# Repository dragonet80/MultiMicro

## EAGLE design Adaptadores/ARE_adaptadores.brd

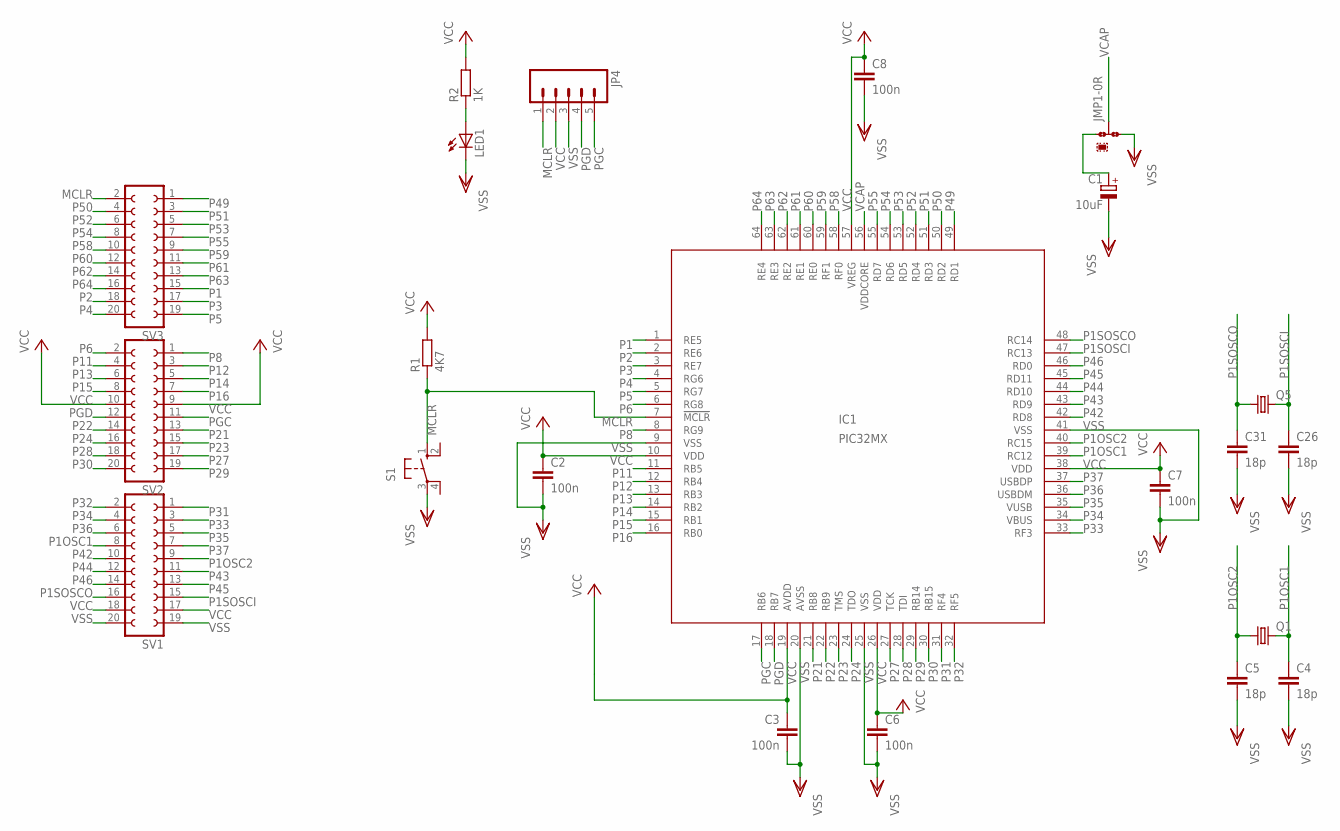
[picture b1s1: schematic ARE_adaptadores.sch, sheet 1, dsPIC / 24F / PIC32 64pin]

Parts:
C1: 10uF; SMC_C
C2, C3, C6, C7, C8: 100n; C0805
C4, C5, C26, C31: 18p; C0805
IC1: PIC32MX; TQFP64-10X10
JMP1: 0R-JUMPA; A0R-JMP
JP4: M05PTH; 1X05
LED1: LEDCHIPLED_0805; CHIPLED_0805
Q1, Q5: CRYSTALHC18U-V; HC18U-V
R1: 4K7; R0805
R2: 1K; R0805
S1: 10-XX; B3F-10XX; MPN B3F-1000
SV1, SV2, SV3: FE10-2W

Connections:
MCLR: IC1.7 (!MCLR), JP4.1, R1.1, S1.1 (S), SV3.2
unnamed: LED1.A, R2.1
unnamed: C1.+, JMP1.1
P1: IC1.1 (RE5), SV3.15
P1OSC1: C4.1, IC1.39 (RC12), Q1.2, SV1.8
P1OSC2: C5.1, IC1.40 (RC15), Q1.1, SV1.9
P1SOSCI: C26.1, IC1.47 (RC13), Q5.2, SV1.15
P1SOSCO: C31.1, IC1.48 (RC14), Q5.1, SV1.16
P2: IC1.2 (RE6), SV3.18
P3: IC1.3 (RE7), SV3.17
P4: IC1.4 (RG6), SV3.20
P5: IC1.5 (RG7), SV3.19
P6: IC1.6 (RG8), SV2.2
P8: IC1.8 (RG9), SV2.1
P11: IC1.11 (RB5), SV2.4
P12: IC1.12 (RB4), SV2.3
P13: IC1.13 (RB3), SV2.6
P14: IC1.14 (RB2), SV2.5
P15: IC1.15 (RB1), SV2.8
P16: IC1.16 (RB0), SV2.7
P21: IC1.21 (RB8), SV2.13
P22: IC1.22 (RB9), SV2.14
P23: IC1.23 (TMS), SV2.15
P24: IC1.24 (TDO), SV2.16
P27: IC1.27 (TCK), SV2.17
P28: IC1.28 (TDI), SV2.18
P29: IC1.29 (RB14), SV2.19
P30: IC1.30 (RB15), SV2.20
P31: IC1.31 (RF4), SV1.1
P32: IC1.32 (RF5), SV1.2
P33: IC1.33 (RF3), SV1.3
P34: IC1.34 (VBUS), SV1.4
P35: IC1.35 (VUSB), SV1.5
P36: IC1.36 (USBDM), SV1.6
P37: IC1.37 (USBDP), SV1.7
P42: IC1.42 (RD8), SV1.10
P43: IC1.43 (RD9), SV1.11
P44: IC1.44 (RD10), SV1.12
P45: IC1.45 (RD11), SV1.13
P46: IC1.46 (RD0), SV1.14
P49: IC1.49 (RD1), SV3.1
P50: IC1.50 (RD2), SV3.4
P51: IC1.51 (RD3), SV3.3
P52: IC1.52 (RD4), SV3.6
P53: IC1.53 (RD5), SV3.5
P54: IC1.54 (RD6), SV3.8
P55: IC1.55 (RD7), SV3.7
P58: IC1.58 (RF0), SV3.10
P59: IC1.59 (RF1), SV3.9
P60: IC1.60 (RE0), SV3.12
P61: IC1.61 (RE1), SV3.11
P62: IC1.62 (RE2), SV3.14
P63: IC1.63 (RE3), SV3.13
P64: IC1.64 (RE4), SV3.16
PGC: IC1.17 (RB6), JP4.5, SV2.11
PGD: IC1.18 (RB7), JP4.4, SV2.12
VCAP: IC1.56 (VDDCORE), JMP1.2
VCC: C2.1, C3.1, C6.1, C7.1, C8.1, IC1.10 (VDD), IC1.19 (AVDD), IC1.26 (VDD), IC1.38 (VDD), IC1.57 (VREG), JP4.2, R1.2, R2.2, SV1.17, SV1.18, SV2.9, SV2.10; also elsewhere on the board
VSS: C1.-, C2.2, C3.2, C4.2, C5.2, C6.2, C7.2, C8.2, C26.2, C31.2, IC1.9 (VSS), IC1.20 (AVSS), IC1.25 (VSS), IC1.41 (VSS), JMP1.3, JP4.3, LED1.C, S1.3, SV1.19, SV1.20; also elsewhere on the board

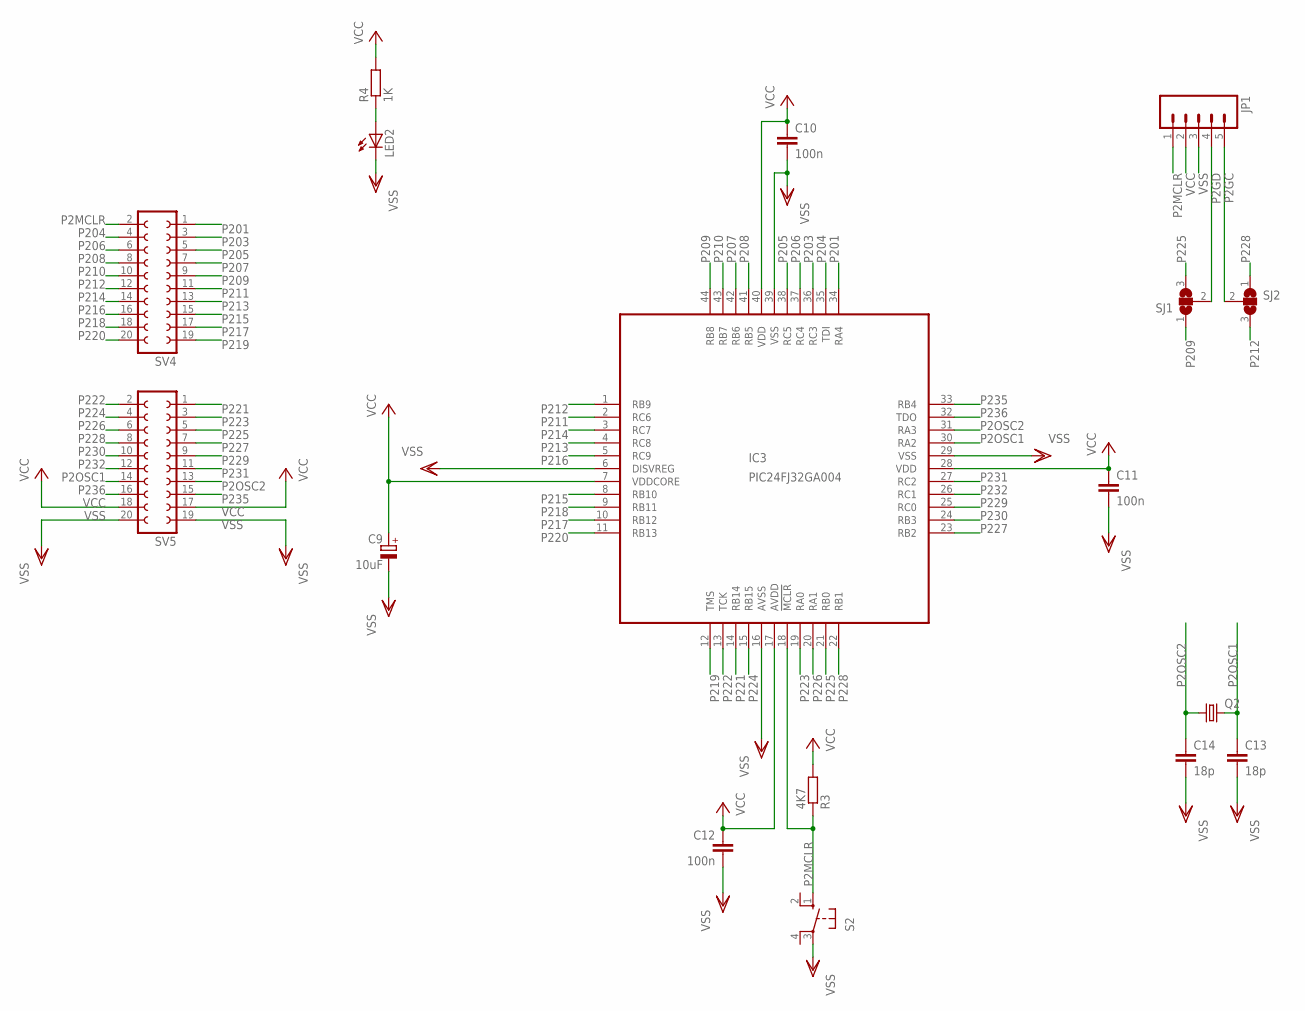
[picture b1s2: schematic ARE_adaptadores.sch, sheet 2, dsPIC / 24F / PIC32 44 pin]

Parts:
C9: 10uF; SMC_C
C10, C11, C12: 100n; C0805
C13, C14: 18p; C0805
IC3: PIC24FJ32GA004; TQFP44
JP1: M05PTH; 1X05
LED2: LEDCHIPLED_0805; CHIPLED_0805
Q2: CRYSTALHC18U-V; HC18U-V
R3: 4K7; R0805
R4: 1K; R0805
S2: 10-XX; B3F-10XX; MPN B3F-1000
SJ1, SJ2: SJ2W; SJ_2
SV4, SV5: FE10-2W

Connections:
unnamed: LED2.A, R4.1
P2GC: JP1.5, SJ2.2
P2GD: JP1.4, SJ1.2
P2MCLR: IC3.18 (!MCLR), JP1.1, R3.1, S2.1 (S), SV4.2
P2OSC1: C13.1, IC3.30 (RA2), Q2.2, SV5.14
P2OSC2: C14.1, IC3.31 (RA3), Q2.1, SV5.13
P201: IC3.34 (RA4), SV4.1
P203: IC3.36 (RC3), SV4.3
P204: IC3.35 (TDI), SV4.4
P205: IC3.38 (RC5), SV4.5
P206: IC3.37 (RC4), SV4.6
P207: IC3.42 (RB6), SV4.7
P208: IC3.41 (RB5), SV4.8
P209: IC3.44 (RB8), SJ1.1, SV4.9
P210: IC3.43 (RB7), SV4.10
P211: IC3.2 (RC6), SV4.11
P212: IC3.1 (RB9), SJ2.3, SV4.12
P213: IC3.4 (RC8), SV4.13
P214: IC3.3 (RC7), SV4.14
P215: IC3.8 (RB10), SV4.15
P216: IC3.5 (RC9), SV4.16
P217: IC3.10 (RB12), SV4.17
P218: IC3.9 (RB11), SV4.18
P219: IC3.12 (TMS), SV4.19
P220: IC3.11 (RB13), SV4.20
P221: IC3.14 (RB14), SV5.1
P222: IC3.13 (TCK), SV5.2
P223: IC3.19 (RA0), SV5.3
P224: IC3.15 (RB15), SV5.4
P225: IC3.21 (RB0), SJ1.3, SV5.5
P226: IC3.20 (RA1), SV5.6
P227: IC3.23 (RB2), SV5.7
P228: IC3.22 (RB1), SJ2.1, SV5.8
P229: IC3.25 (RC0), SV5.9
P230: IC3.24 (RB3), SV5.10
P231: IC3.27 (RC2), SV5.11
P232: IC3.26 (RC1), SV5.12
P235: IC3.33 (RB4), SV5.15
P236: IC3.32 (TDO), SV5.16
VCC: C9.+, C10.1, C11.1, C12.1, IC3.7 (VDDCORE), IC3.17 (AVDD), IC3.28 (VDD), IC3.40 (VDD), JP1.2, R3.2, R4.2, SV5.17, SV5.18; also elsewhere on the board
VSS: C9.-, C10.2, C11.2, C12.2, C13.2, C14.2, IC3.6 (DISVREG), IC3.16 (AVSS), IC3.29 (VSS), IC3.39 (VSS), JP1.3, LED2.C, S2.3, SV5.19, SV5.20; also elsewhere on the board

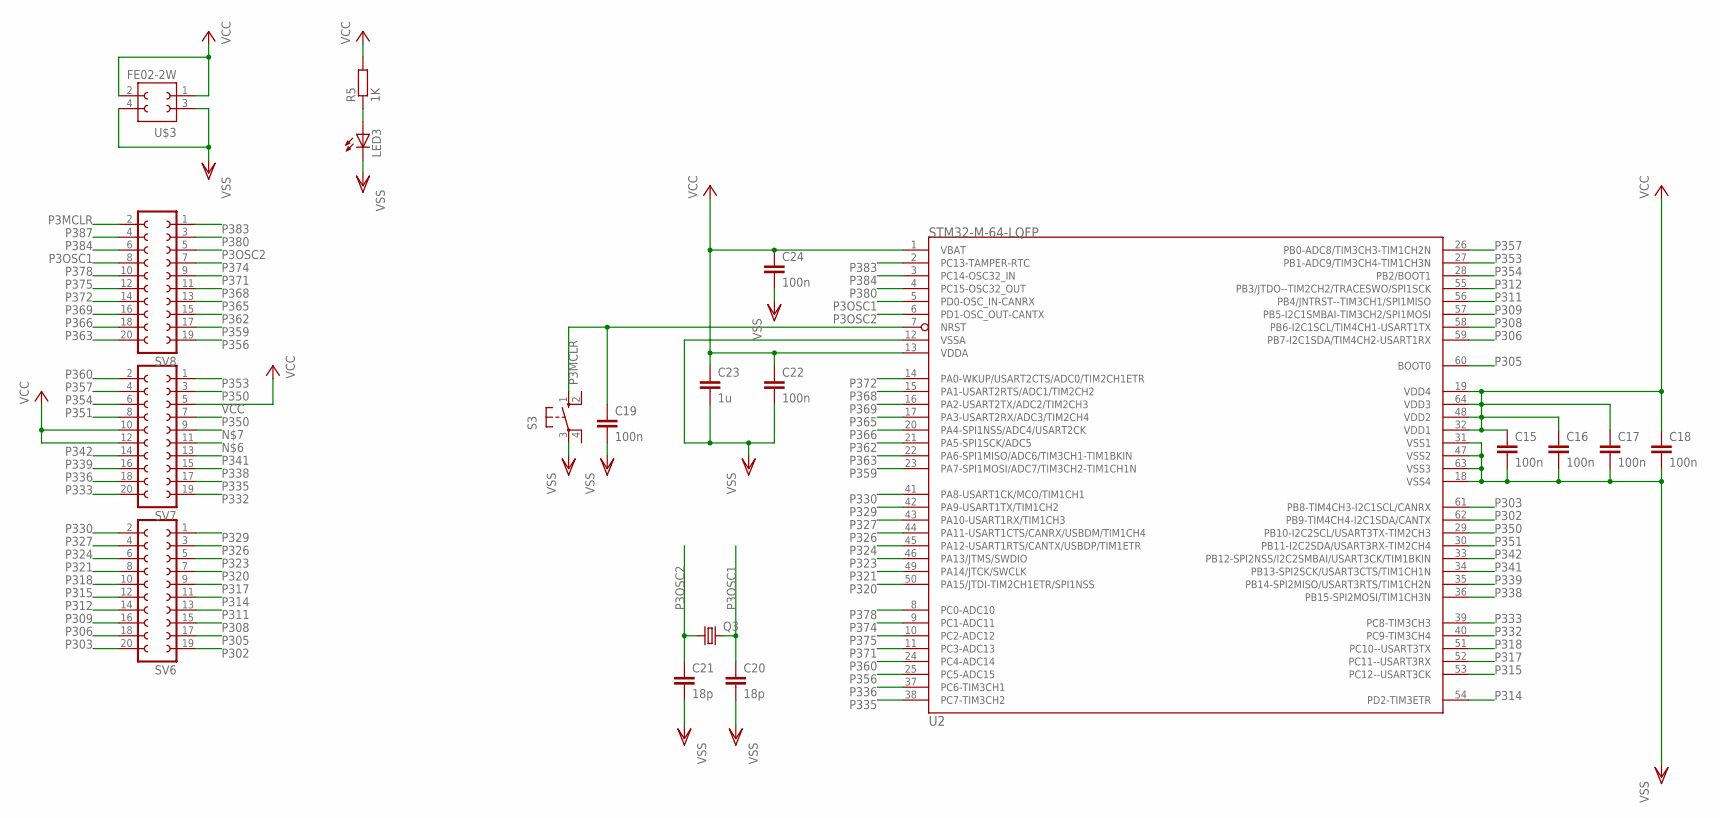
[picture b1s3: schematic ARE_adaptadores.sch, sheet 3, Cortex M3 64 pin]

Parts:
C15, C16, C17, C18, C19, C22, C24: 100n; C0805
C20, C21: 18p; C0805
C23: 1u; C0805
LED3: LEDCHIPLED_0805; CHIPLED_0805
Q3: CRYSTALHC18U-V; HC18U-V
R5: 1K; R0805
S3: 10-XX; B3F-10XX; MPN B3F-1000
SV6, SV7, SV8: FE10-2W
U2: STM32-M-64-LQFP; LQFP64
U$3: FE02-2W

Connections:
unnamed: LED3.A, R5.1
P3MCLR: C19.1, S3.1 (S), SV8.2, U2.7 (NRST)
P3OSC1: C20.1, Q3.2, SV8.8, U2.5 (PD0-OSC_IN-CANRX)
P3OSC2: C21.1, Q3.1, SV8.5, U2.6 (PD1-OSC_OUT-CANTX)
P302: SV6.19, U2.62 (PB9-TIM4CH4-I2C1SDA/CANTX)
P303: SV6.20, U2.61 (PB8-TIM4CH3-I2C1SCL/CANRX)
P305: SV6.17, U2.60 (BOOT0)
P306: SV6.18, U2.59 (PB7-I2C1SDA/TIM4CH2-USART1RX)
P308: SV6.15, U2.58 (PB6-I2C1SCL/TIM4CH1-USART1TX)
P309: SV6.16, U2.57 (PB5-I2C1SMBAI-TIM3CH2/SPI1MOSI)
P311: SV6.13, U2.56 (PB4/JNTRST--TIM3CH1/SPI1MISO)
P312: SV6.14, U2.55 (PB3/JTDO--TIM2CH2/TRACESWO/SPI1SCK)
P314: SV6.11, U2.54 (PD2-TIM3ETR)
P315: SV6.12, U2.53 (PC12--USART3CK)
P317: SV6.9, U2.52 (PC11--USART3RX)
P318: SV6.10, U2.51 (PC10--USART3TX)
P320: SV6.7, U2.50 (PA15/JTDI-TIM2CH1ETR/SPI1NSS)
P321: SV6.8, U2.49 (PA14/JTCK/SWCLK)
P323: SV6.5, U2.46 (PA13/JTMS/SWDIO)
P324: SV6.6, U2.45 (PA12-USART1RTS/CANTX/USBDP/TIM1ETR)
P326: SV6.3, U2.44 (PA11-USART1CTS/CANRX/USBDM/TIM1CH4)
P327: SV6.4, U2.43 (PA10-USART1RX/TIM1CH3)
P329: SV6.1, U2.42 (PA9-USART1TX/TIM1CH2)
P330: SV6.2, U2.41 (PA8-USART1CK/MCO/TIM1CH1)
P332: SV7.19, U2.40 (PC9-TIM3CH4)
P333: SV7.20, U2.39 (PC8-TIM3CH3)
P335: SV7.17, U2.38 (PC7-TIM3CH2)
P336: SV7.18, U2.37 (PC6-TIM3CH1)
P338: SV7.15, U2.36 (PB15-SPI2MOSI/TIM1CH3N)
P339: SV7.16, U2.35 (PB14-SPI2MISO/USART3RTS/TIM1CH2N)
P341: SV7.13, U2.34 (PB13-SPI2SCK/USART3CTS/TIM1CH1N)
P342: SV7.14, U2.33 (PB12-SPI2NSS/I2C2SMBAI/USART3CK/TIM1BKIN)
P350: SV7.3, SV7.7, U2.29 (PB10-I2C2SCL/USART3TX-TIM2CH3)
P351: SV7.8, U2.30 (PB11-I2C2SDA/USART3RX-TIM2CH4)
P353: SV7.1, U2.27 (PB1-ADC9/TIM3CH4-TIM1CH3N)
P354: SV7.6, U2.28 (PB2/BOOT1)
P356: SV8.19, U2.25 (PC5-ADC15)
P357: SV7.4, U2.26 (PB0-ADC8/TIM3CH3-TIM1CH2N)
P359: SV8.17, U2.23 (PA7-SPI1MOSI/ADC7/TIM3CH2-TIM1CH1N)
P360: SV7.2, U2.24 (PC4-ADC14)
P362: SV8.15, U2.21 (PA5-SPI1SCK/ADC5)
P363: SV8.20, U2.22 (PA6-SPI1MISO/ADC6/TIM3CH1-TIM1BKIN)
P365: SV8.13, U2.17 (PA3-USART2RX/ADC3/TIM2CH4)
P366: SV8.18, U2.20 (PA4-SPI1NSS/ADC4/USART2CK)
P368: SV8.11, U2.15 (PA1-USART2RTS/ADC1/TIM2CH2)
P369: SV8.16, U2.16 (PA2-USART2TX/ADC2/TIM2CH3)
P371: SV8.9, U2.11 (PC3-ADC13)
P372: SV8.14, U2.14 (PA0-WKUP/USART2CTS/ADC0/TIM2CH1ETR)
P374: SV8.7, U2.9 (PC1-ADC11)
P375: SV8.12, U2.10 (PC2-ADC12)
P378: SV8.10, U2.8 (PC0-ADC10)
P380: SV8.3, U2.4 (PC15-OSC32_OUT)
P383: SV8.1, U2.2 (PC13-TAMPER-RTC)
P384: SV8.6, U2.3 (PC14-OSC32_IN)
P387: SV8.4
VCC: C15.1, C16.1, C17.1, C18.1, C22.1, C23.1, C24.1, R5.2, SV7.5, SV7.10, SV7.12, U2.1 (VBAT), U2.13 (VDDA), U2.19 (VDD4), U2.32 (VDD1), U2.48 (VDD2), U2.64 (VDD3), U$3.1, U$3.2; also elsewhere on the board
VSS: C15.2, C16.2, C17.2, C18.2, C19.2, C20.2, C21.2, C22.2, C23.2, C24.2, LED3.C, S3.3, U2.12 (VSSA), U2.18 (VSS4), U2.31 (VSS1), U2.47 (VSS2), U2.63 (VSS3), U$3.3, U$3.4; also elsewhere on the board

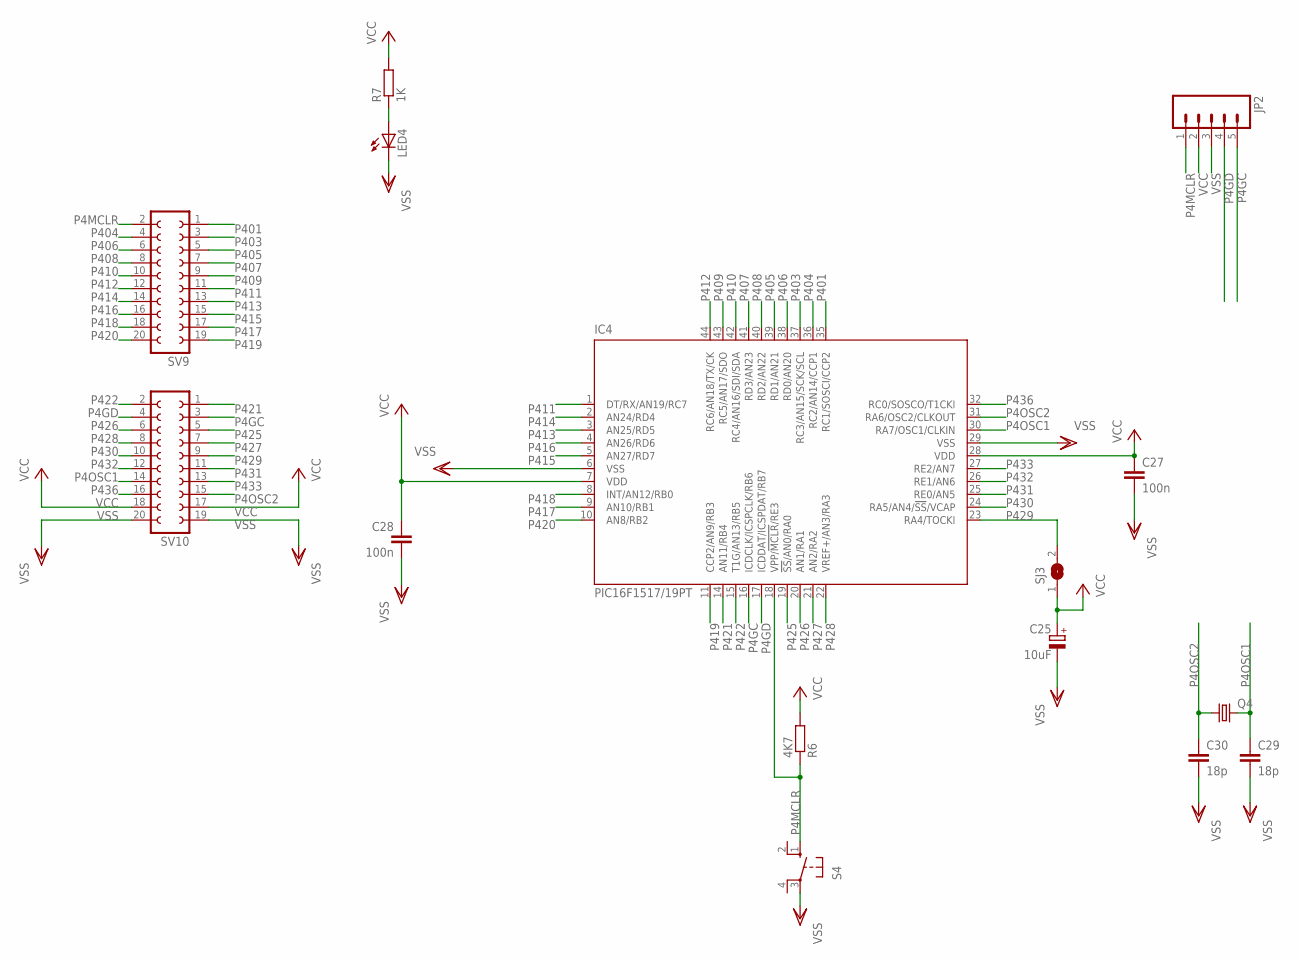
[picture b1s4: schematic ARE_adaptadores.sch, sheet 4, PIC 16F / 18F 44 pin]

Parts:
C25: 10uF; SMC_C
C27, C28: 100n; C0805
C29, C30: 18p; C0805
IC4: PIC16F1517/19PT; TQFP44
JP2: M05PTH; 1X05
LED4: LEDCHIPLED_0805; CHIPLED_0805
Q4: CRYSTALHC18U-V; HC18U-V
R6: 4K7; R0805
R7: 1K; R0805
S4: 10-XX; B3F-10XX; MPN B3F-1000
SJ3: SJ
SV9, SV10: FE10-2W

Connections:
unnamed: LED4.A, R7.1
P4GC: IC4.16 (ICDCLK/ICSPCLK/RB6), JP2.5, SV10.3
P4GD: IC4.17 (ICDDAT/ICSPDAT/RB7), JP2.4, SV10.4
P4MCLR: IC4.18 (VPP/!MCLR!/RE3), JP2.1, R6.1, S4.1 (S), SV9.2
P4OSC1: C29.1, IC4.30 (RA7/OSC1/CLKIN), Q4.2, SV10.14
P4OSC2: C30.1, IC4.31 (RA6/OSC2/CLKOUT), Q4.1, SV10.15
P401: IC4.35 (RC1/SOSCI/CCP2), SV9.1
P403: IC4.37 (RC3/AN15/SCK/SCL), SV9.3
P404: IC4.36 (RC2/AN14/CCP1), SV9.4
P405: IC4.39 (RD1/AN21), SV9.5
P406: IC4.38 (RD0/AN20), SV9.6
P407: IC4.41 (RD3/AN23), SV9.7
P408: IC4.40 (RD2/AN22), SV9.8
P409: IC4.43 (RC5/AN17/SDO), SV9.9
P410: IC4.42 (RC4/AN16/SDI/SDA), SV9.10
P411: IC4.1 (DT/RX/AN19/RC7), SV9.11
P412: IC4.44 (RC6/AN18/TX/CK), SV9.12
P413: IC4.3 (AN25/RD5), SV9.13
P414: IC4.2 (AN24/RD4), SV9.14
P415: IC4.5 (AN27/RD7), SV9.15
P416: IC4.4 (AN26/RD6), SV9.16
P417: IC4.9 (AN10/RB1), SV9.17
P418: IC4.8 (INT/AN12/RB0), SV9.18
P419: IC4.11 (CCP2/AN9/RB3), SV9.19
P420: IC4.10 (AN8/RB2), SV9.20
P421: IC4.14 (AN11/RB4), SV10.1
P422: IC4.15 (T1G/AN13/RB5), SV10.2
P425: IC4.19 (!SS!/AN0/RA0), SV10.5
P426: IC4.20 (AN1/RA1), SV10.6
P427: IC4.21 (AN2/RA2), SV10.7
P428: IC4.22 (VREF+/AN3/RA3), SV10.8
P429: IC4.23 (RA4/TOCKI), SJ3.2, SV10.9
P430: IC4.24 (RA5/AN4/!SS!/VCAP), SV10.10
P431: IC4.25 (RE0/AN5), SV10.11
P432: IC4.26 (RE1/AN6), SV10.12
P433: IC4.27 (RE2/AN7), SV10.13
P436: IC4.32 (RC0/SOSCO/T1CKI), SV10.16
VCC: C25.+, C27.1, C28.1, IC4.7 (VDD), IC4.28 (VDD), JP2.2, R6.2, R7.2, SJ3.1, SV10.17, SV10.18; also elsewhere on the board
VSS: C25.-, C27.2, C28.2, C29.2, C30.2, IC4.6 (VSS), IC4.29 (VSS), JP2.3, LED4.C, S4.3, SV10.19, SV10.20; also elsewhere on the board

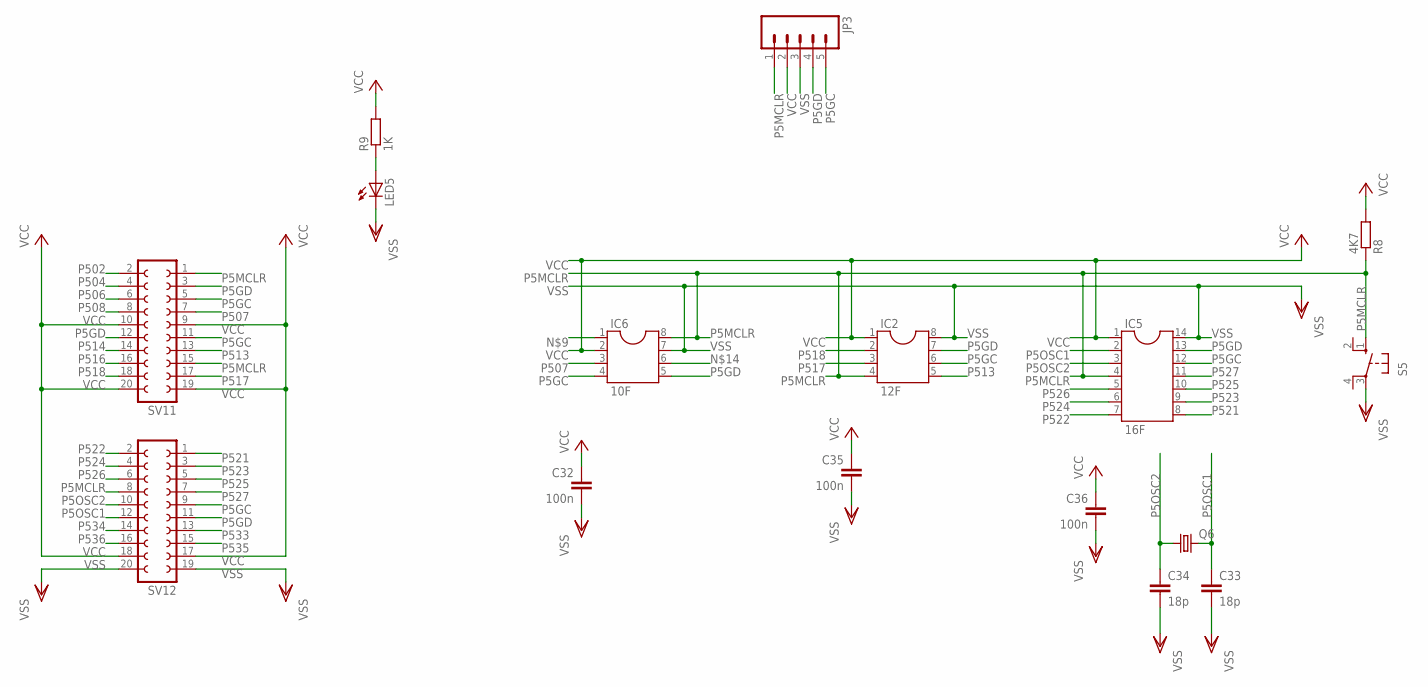
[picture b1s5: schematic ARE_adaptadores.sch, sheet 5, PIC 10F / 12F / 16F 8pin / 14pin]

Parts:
C32, C35, C36: 100n; C0805
C33, C34: 18p; C0805
IC2: 12F; SOCKET-08
IC5: 16F; SOCKET-14
IC6: 10F; SOCKET-08
JP3: M05PTH; 1X05
LED5: LEDCHIPLED_0805; CHIPLED_0805
Q6: CRYSTALHC18U-V; HC18U-V
R8: 4K7; R0805
R9: 1K; R0805
S5: 10-XX; B3F-10XX; MPN B3F-1000
SV11, SV12: FE10-2W

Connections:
unnamed: LED5.A, R9.1
P5GC: IC2.6, IC5.12, IC6.4, JP3.5, SV11.5, SV11.11, SV12.9
P5GD: IC2.7, IC5.13, IC6.5, JP3.4, SV11.3, SV11.12, SV12.11
P5MCLR: IC2.4, IC5.4, IC6.8, JP3.1, R8.1, S5.1 (S), SV11.1, SV11.15, SV12.8
P5OSC1: C33.1, IC5.2, Q6.2, SV12.12
P5OSC2: C34.1, IC5.3, Q6.1, SV12.10
P502: SV11.2
P504: SV11.4
P506: SV11.6
P507: IC6.3, SV11.7
P508: SV11.8
P513: IC2.5, SV11.13
P514: SV11.14
P516: SV11.16
P517: IC2.3, SV11.17
P518: IC2.2, SV11.18
P521: IC5.8, SV12.1
P522: IC5.7, SV12.2
P523: IC5.9, SV12.3
P524: IC5.6, SV12.4
P525: IC5.10, SV12.5
P526: IC5.5, SV12.6
P527: IC5.11, SV12.7
P533: SV12.13
P534: SV12.14
P535: SV12.15
P536: SV12.16
VCC: C32.1, C35.1, C36.1, IC2.1, IC5.1, IC6.2, JP3.2, R8.2, R9.2, SV11.9, SV11.10, SV11.19, SV11.20, SV12.17, SV12.18; also elsewhere on the board
VSS: C32.2, C33.2, C34.2, C35.2, C36.2, IC2.8, IC5.14, IC6.7, JP3.3, LED5.C, S5.3, SV12.19, SV12.20; also elsewhere on the board

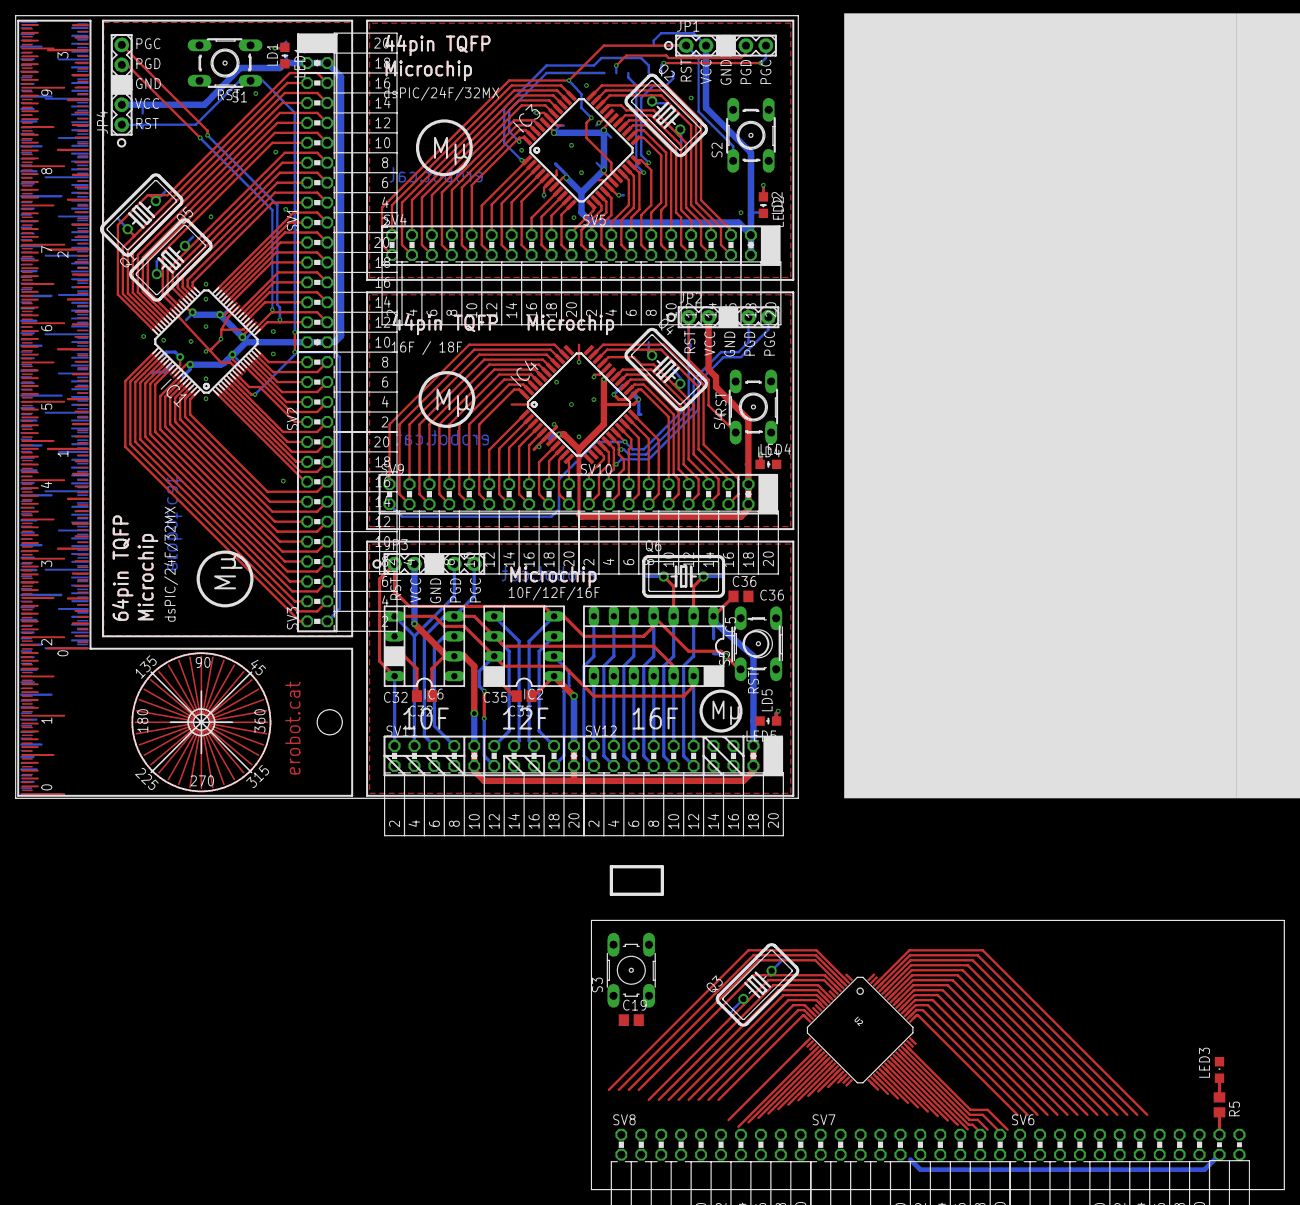
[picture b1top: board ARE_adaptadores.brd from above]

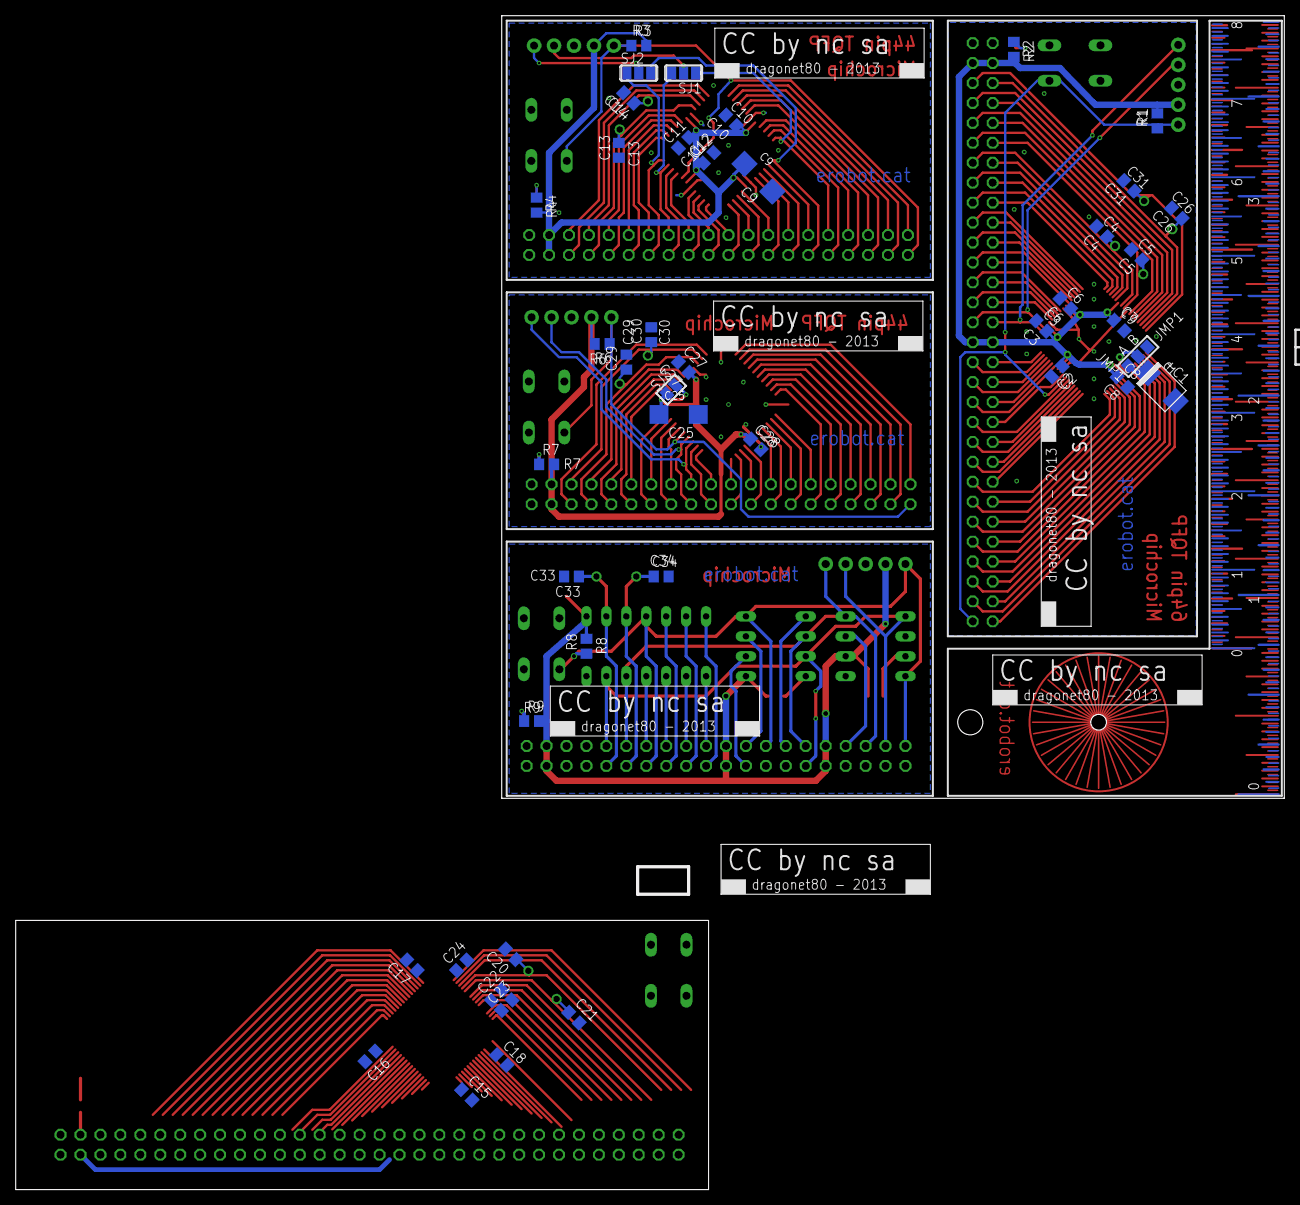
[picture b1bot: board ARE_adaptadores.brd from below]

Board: 2 copper layers, 161.6 x 149.5 mm, 89 parts (44 on the bottom side), 206 nets.

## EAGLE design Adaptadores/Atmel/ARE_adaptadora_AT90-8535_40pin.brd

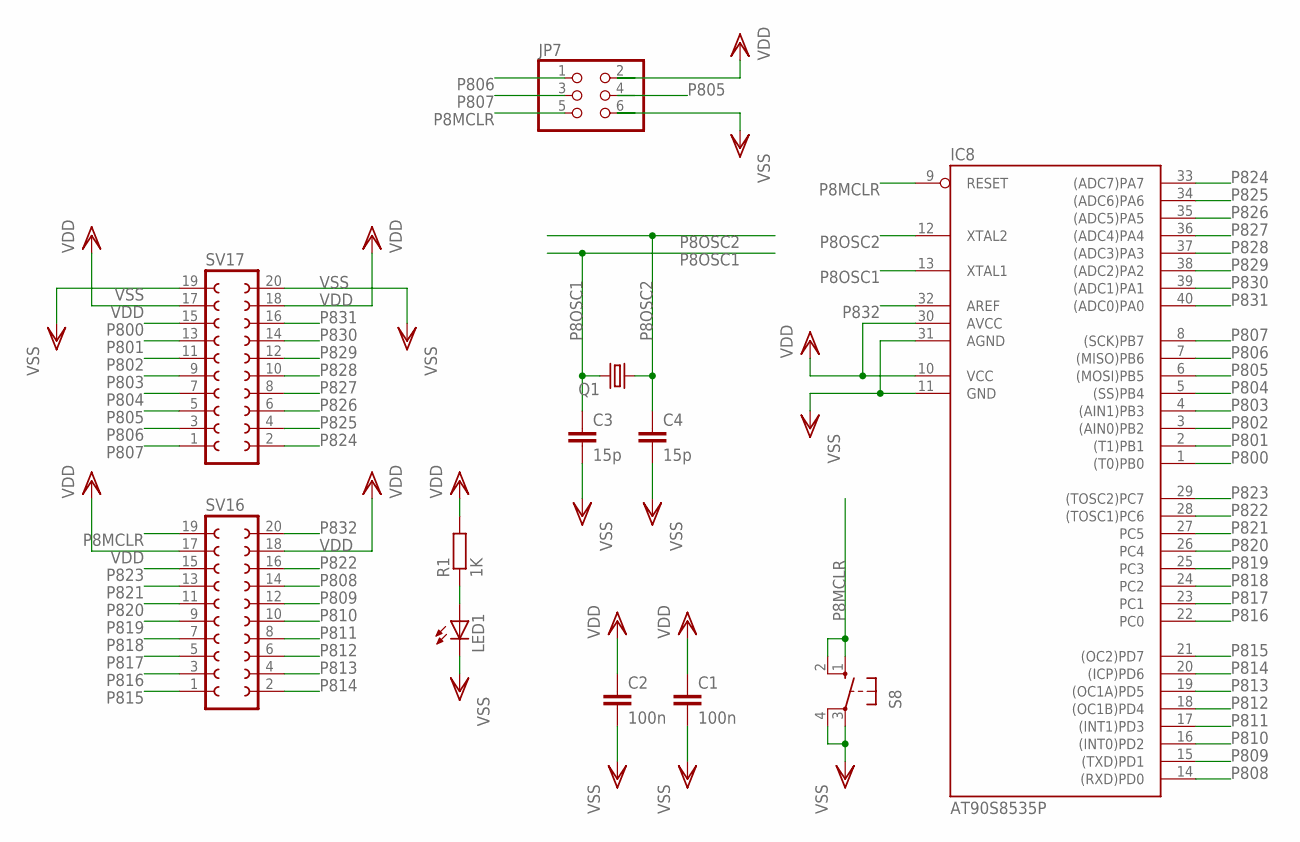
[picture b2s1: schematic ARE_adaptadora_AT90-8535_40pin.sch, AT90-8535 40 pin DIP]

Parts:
C1, C2: 100n; C0805
C3, C4: 15p; C0805
IC8: AT90S8535P; DIL40
JP7: PINHD-2X3; 2X03
LED1: LED3MM
Q1: CRYSTALHC18U-V; HC18U-V
R1: 1K; R0805
S8: 10-XX; B3F-10XX; MPN B3F-1000
SV16, SV17: FE10-2W

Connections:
unnamed: LED1.A, R1.1
P8MCLR: IC8.9 (RESET), JP7.5, S8.1 (S), S8.2 (S1), SV16.19
P8OSC1: C3.1, IC8.13 (XTAL1), Q1.2
P8OSC2: C4.1, IC8.12 (XTAL2), Q1.1
P800: IC8.1 ((T0)PB0), SV17.15
P801: IC8.2 ((T1)PB1), SV17.13
P802: IC8.3 ((AIN0)PB2), SV17.11
P803: IC8.4 ((AIN1)PB3), SV17.9
P804: IC8.5 ((SS)PB4), SV17.7
P805: IC8.6 ((MOSI)PB5), JP7.4, SV17.5
P806: IC8.7 ((MISO)PB6), JP7.1, SV17.3
P807: IC8.8 ((SCK)PB7), JP7.3, SV17.1
P808: IC8.14 ((RXD)PD0), SV16.14
P809: IC8.15 ((TXD)PD1), SV16.12
P810: IC8.16 ((INT0)PD2), SV16.10
P811: IC8.17 ((INT1)PD3), SV16.8
P812: IC8.18 ((OC1B)PD4), SV16.6
P813: IC8.19 ((OC1A)PD5), SV16.4
P814: IC8.20 ((ICP)PD6), SV16.2
P815: IC8.21 ((OC2)PD7), SV16.1
P816: IC8.22 (PC0), SV16.3
P817: IC8.23 (PC1), SV16.5
P818: IC8.24 (PC2), SV16.7
P819: IC8.25 (PC3), SV16.9
P820: IC8.26 (PC4), SV16.11
P821: IC8.27 (PC5), SV16.13
P822: IC8.28 ((TOSC1)PC6), SV16.16
P823: IC8.29 ((TOSC2)PC7), SV16.15
P824: IC8.33 ((ADC7)PA7), SV17.2
P825: IC8.34 ((ADC6)PA6), SV17.4
P826: IC8.35 ((ADC5)PA5), SV17.6
P827: IC8.36 ((ADC4)PA4), SV17.8
P828: IC8.37 ((ADC3)PA3), SV17.10
P829: IC8.38 ((ADC2)PA2), SV17.12
P830: IC8.39 ((ADC1)PA1), SV17.14
P831: IC8.40 ((ADC0)PA0), SV17.16
P832: IC8.32 (AREF), SV16.20
VDD: C1.1, C2.1, IC8.10 (VCC), IC8.30 (AVCC), JP7.2, R1.2, SV16.17, SV16.18, SV17.17, SV17.18
VSS: C1.2, C2.2, C3.2, C4.2, IC8.11 (GND), IC8.31 (AGND), JP7.6, LED1.K (C), S8.3, S8.4 (P1), SV17.19, SV17.20

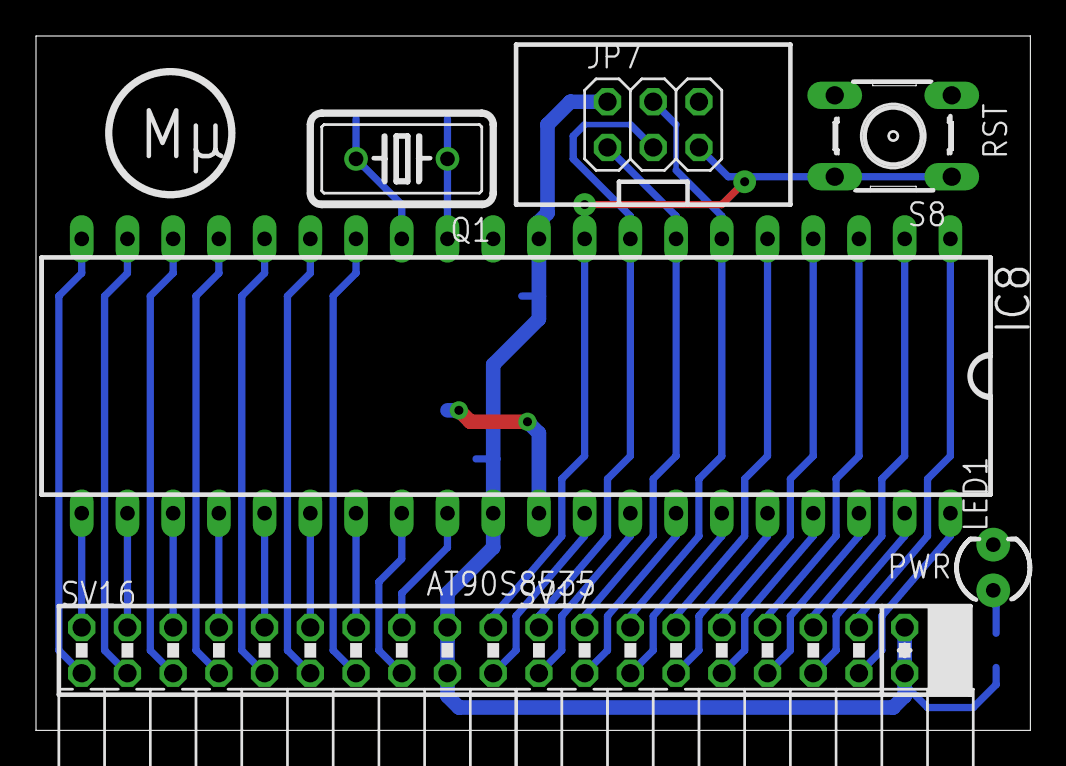
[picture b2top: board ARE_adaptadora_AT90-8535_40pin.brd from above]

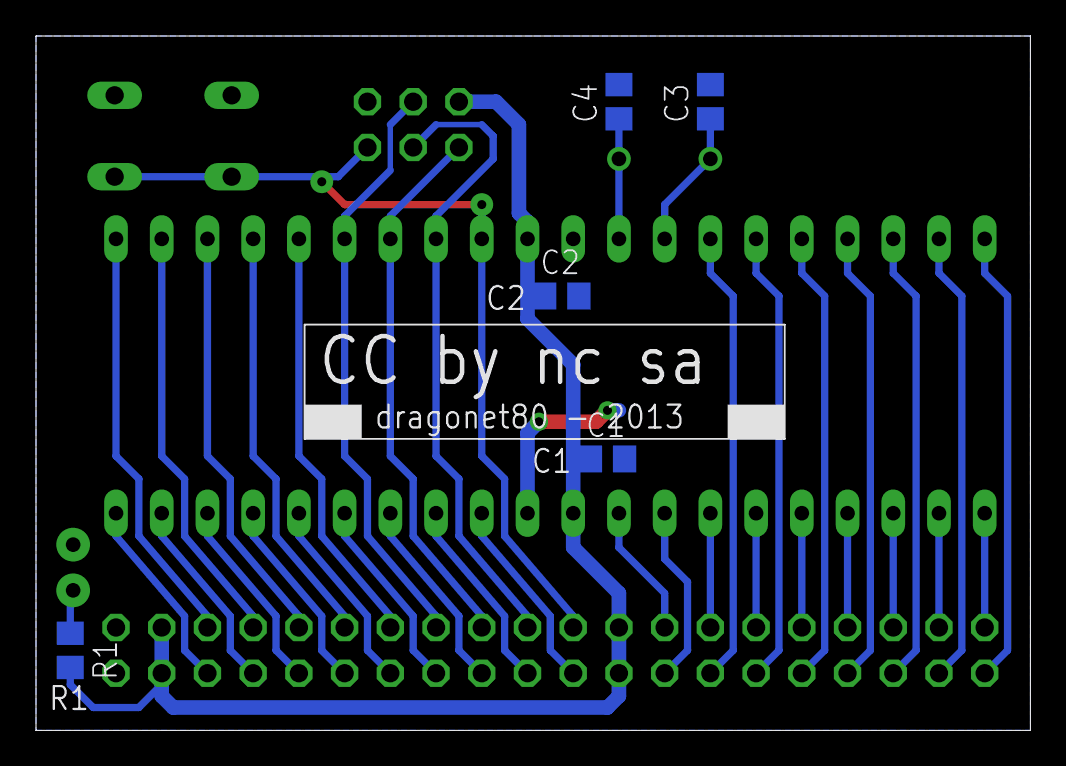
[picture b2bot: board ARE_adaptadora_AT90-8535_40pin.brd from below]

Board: 2 copper layers, 55.2 x 38.6 mm, 12 parts (5 on the bottom side), 39 nets.

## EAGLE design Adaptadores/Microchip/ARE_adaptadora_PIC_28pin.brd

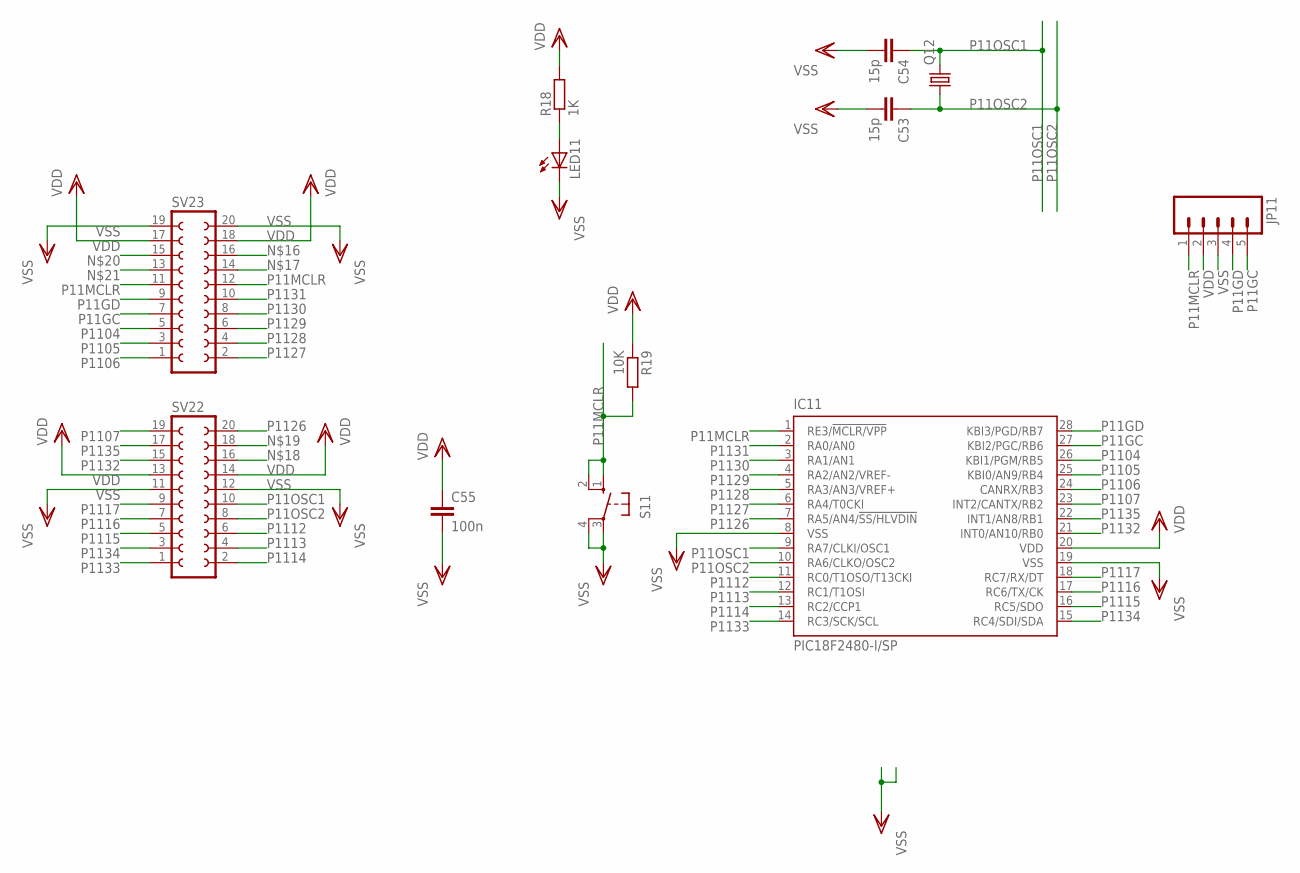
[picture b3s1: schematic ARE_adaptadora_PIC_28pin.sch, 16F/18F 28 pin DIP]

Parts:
C53, C54: 15p; C0805
C55: 100n; C0805
IC11: PIC18F2480-I/SP; DIL28-3
JP11: M05PTH; 1X05
LED11: LED3MM
Q12: CRYSTALHC18U-V; HC18U-V
R18: 1K; R0805
R19: 10K; R0805
S11: 10-XX; B3F-10XX; MPN B3F-1000
SV22, SV23: FE10-2W

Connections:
unnamed: LED11.A, R18.1
P11GC: IC11.27 (KBI2/PGC/RB6), JP11.5, SV23.7
P11GD: IC11.28 (KBI3/PGD/RB7), JP11.4, SV23.9
P11MCLR: IC11.1 (RE3/!MCLR/VPP), JP11.1, R19.2, S11.1 (S), S11.2 (S1), SV23.11, SV23.12
P11OSC1: C54.1, IC11.9 (RA7/CLKI/OSC1), Q12.2, SV22.10
P11OSC2: C53.1, IC11.10 (RA6/CLKO/OSC2), Q12.1, SV22.8
P1104: IC11.26 (KBI1/PGM/RB5), SV23.5
P1105: IC11.25 (KBI0/AN9/RB4), SV23.3
P1106: IC11.24 (CANRX/RB3), SV23.1
P1107: IC11.23 (INT2/CANTX/RB2), SV22.19
P1112: IC11.11 (RC0/T1OSO/T13CKI), SV22.6
P1113: IC11.12 (RC1/T1OSI), SV22.4
P1114: IC11.13 (RC2/CCP1), SV22.2
P1115: IC11.16 (RC5/SDO), SV22.5
P1116: IC11.17 (RC6/TX/CK), SV22.7
P1117: IC11.18 (RC7/RX/DT), SV22.9
P1126: IC11.7 (RA5/AN4/!SS/HLVDIN), SV22.20
P1127: IC11.6 (RA4/T0CKI), SV23.2
P1128: IC11.5 (RA3/AN3/VREF+), SV23.4
P1129: IC11.4 (RA2/AN2/VREF-), SV23.6
P1130: IC11.3 (RA1/AN1), SV23.8
P1131: IC11.2 (RA0/AN0), SV23.10
P1132: IC11.21 (INT0/AN10/RB0), SV22.15
P1133: IC11.14 (RC3/SCK/SCL), SV22.1
P1134: IC11.15 (RC4/SDI/SDA), SV22.3
P1135: IC11.22 (INT1/AN8/RB1), SV22.17
VDD: C55.1, IC11.20 (VDD), JP11.2, R18.2, R19.1, SV22.13, SV22.14, SV23.17, SV23.18
VSS: C53.2, C54.2, C55.2, IC11.8 (VSS), IC11.19 (VSS), JP11.3, LED11.K (C), S11.3, S11.4 (P1), SV22.11, SV22.12, SV23.19, SV23.20

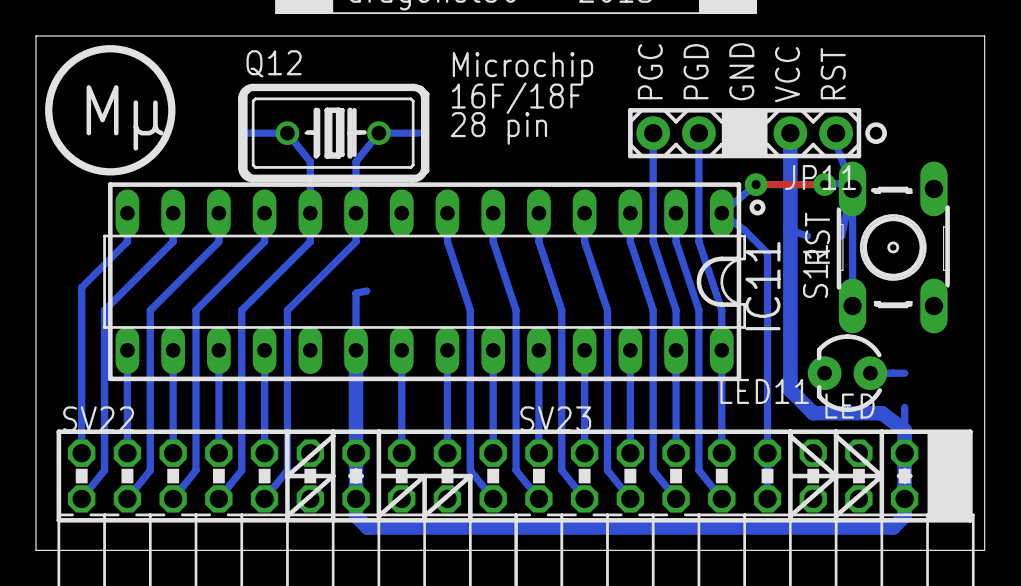
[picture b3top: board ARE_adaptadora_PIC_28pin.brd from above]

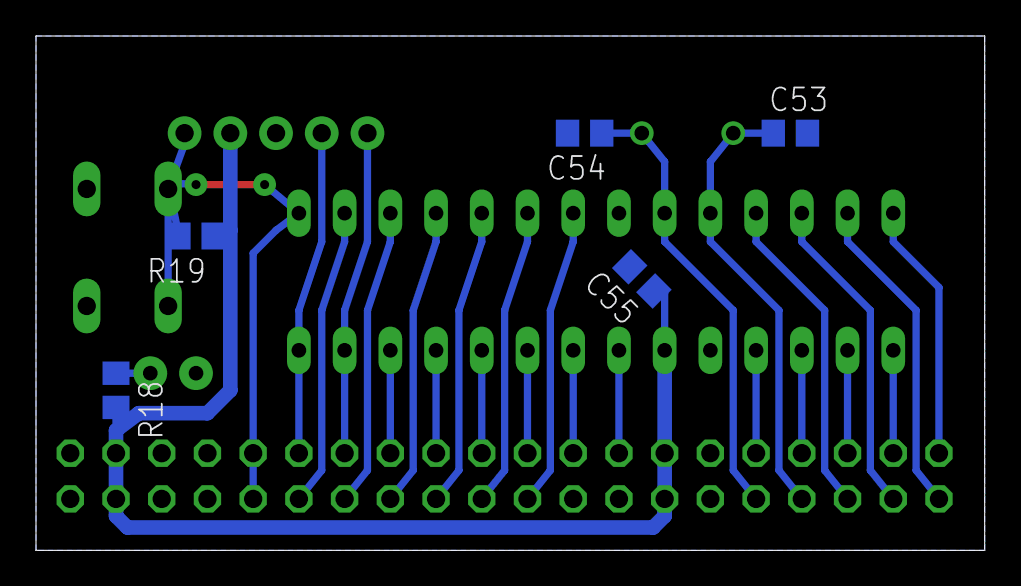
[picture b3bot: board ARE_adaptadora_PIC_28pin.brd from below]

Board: 2 copper layers, 52.7 x 28.6 mm, 12 parts (5 on the bottom side), 28 nets.

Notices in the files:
Adaptadores/ARE_adaptadores.brd:
CC by nc sa
